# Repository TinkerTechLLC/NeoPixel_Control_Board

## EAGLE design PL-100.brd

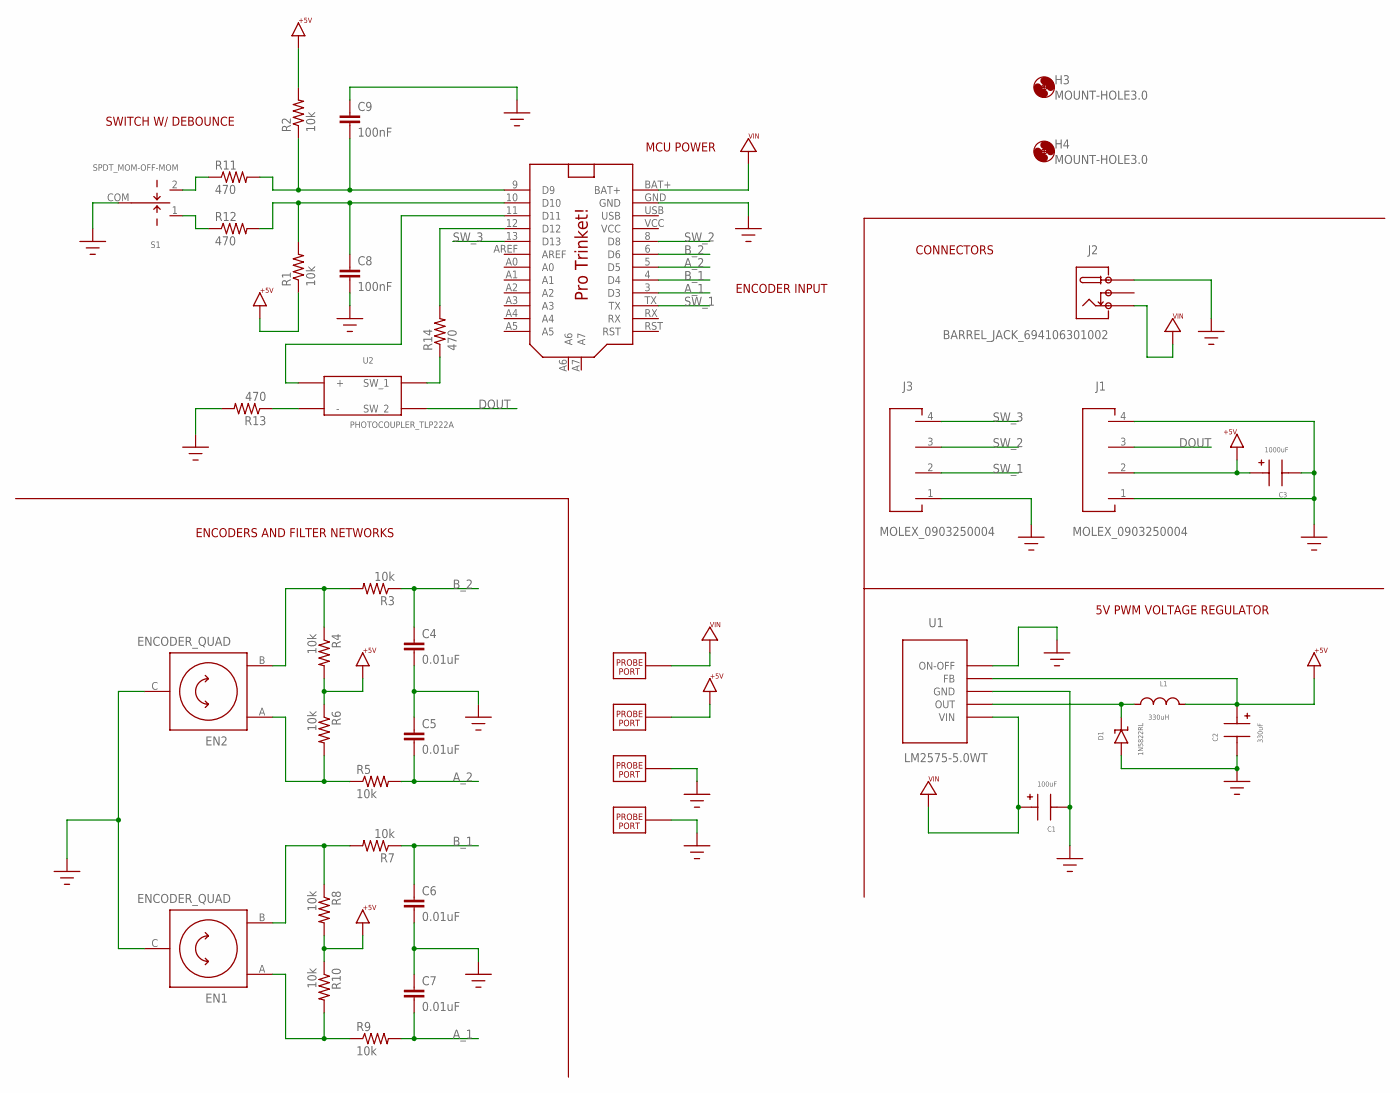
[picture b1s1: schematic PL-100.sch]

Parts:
+5V: PROBE_PORT
C1: 100uF; RADIAL_POL_6.3-DIA_2.5-SPACE
C2: 330uF; RADIAL_POL_8-DIA_3.5-SPACE
C3: 1000uF; RADIAL_POL_10-DIA_5-SPACE
C4, C5, C6, C7: 0.01uF; CAP-PTH-SMALLEZ
C8, C9: 100nF; CAP-PTH-SMALL
D1: 1N5822RL; DO-201AD_AXIAL
EN1, EN2: ENCODER_QUAD; PEC11R-4015F-N0024
GND1, GND2: PROBE_PORT
H3, H4: MOUNT-HOLE3.0; 3,0
J1, J3: MOLEX_0903250004; 0903250004
J2: BARREL_JACK_694106301002
L1: 330uH; INDUCT_AXIAL_28-SPACING
R1, R2, R3, R4, R5, R6, R7, R8, R9, R10: 10k; AXIAL-0.4
R11, R12, R13, R14: 470; AXIAL-0.4
S1: SPDT_MOM-OFF-MOM; 100SP4T6B11M2QEH
U1: LM2575-5.0WT; TO-220-5
U2: PHOTOCOUPLER_TLP222A; DIP-4
U$2: PRO_TRINKET; PROTRINKET
VIN: PROBE_PORT

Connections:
3: J2.3
+5V: +5V.P$1, C2.+, C3.+, J1.2, L1.2, R1.P$1 (1), R2.P$2 (2), R4.P$2 (2), R6.P$1 (1), R8.P$2 (2), R10.P$1 (1), U1.4 (FB)
A_1: C7.2, R9.P$2 (2), U$2.3 (D3)
A_2: C5.2, R5.P$2 (2), U$2.5 (D5)
B_1: C6.1, R7.P$1 (1), U$2.4 (D4)
B_2: C4.1, R3.P$1 (1), U$2.6 (D6)
DOUT: J1.3, U2.4 (SW_2)
GND: C1.-, C2.-, C3.-, C4.2, C5.1, C6.2, C7.1, C8.2, C9.1, D1.+, EN1.C (2), EN2.C (2), GND1.P$1, GND2.P$1, J1.1, J1.4, J2.1, J3.1, R13.P$2 (2), S1.COM, U1.3 (GND), U1.5 (ON-OFF), U$2.GND
unnamed: D1.-, L1.1, U1.2 (OUT)
unnamed: C9.2, R2.P$1 (1), R11.P$2 (2), U$2.9 (D9)
unnamed: C8.1, R1.P$2 (2), R12.P$2 (2), U$2.10 (D10)
unnamed: EN2.B (3), R3.P$2 (2), R4.P$1 (1)
unnamed: EN2.A (1), R5.P$1 (1), R6.P$2 (2)
unnamed: EN1.B (3), R7.P$2 (2), R8.P$1 (1)
unnamed: EN1.A (1), R9.P$1 (1), R10.P$2 (2)
unnamed: R11.P$1 (1), S1.2 (MOM_2)
unnamed: R12.P$1 (1), S1.1 (MOM_1)
unnamed: R13.P$1 (1), U2.2 (-)
unnamed: R14.P$2 (2), U$2.12 (D12)
unnamed: R14.P$1 (1), U2.3 (SW_1)
unnamed: U2.1 (+), U$2.11 (D11)
SW_1: J3.2, U$2.TX
SW_2: J3.3, U$2.8 (D8)
SW_3: J3.4, U$2.13 (D13)
USB: U$2.USB
VCC: U$2.VCC
VIN: C1.+, J2.2, U1.1 (VIN), U$2.BAT+, VIN.P$1

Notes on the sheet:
5V PWM VOLTAGE REGULATOR
ENCODERS AND FILTER NETWORKS
CONNECTORS
SWITCH W/ DEBOUNCE
ENCODER INPUT
MCU POWER

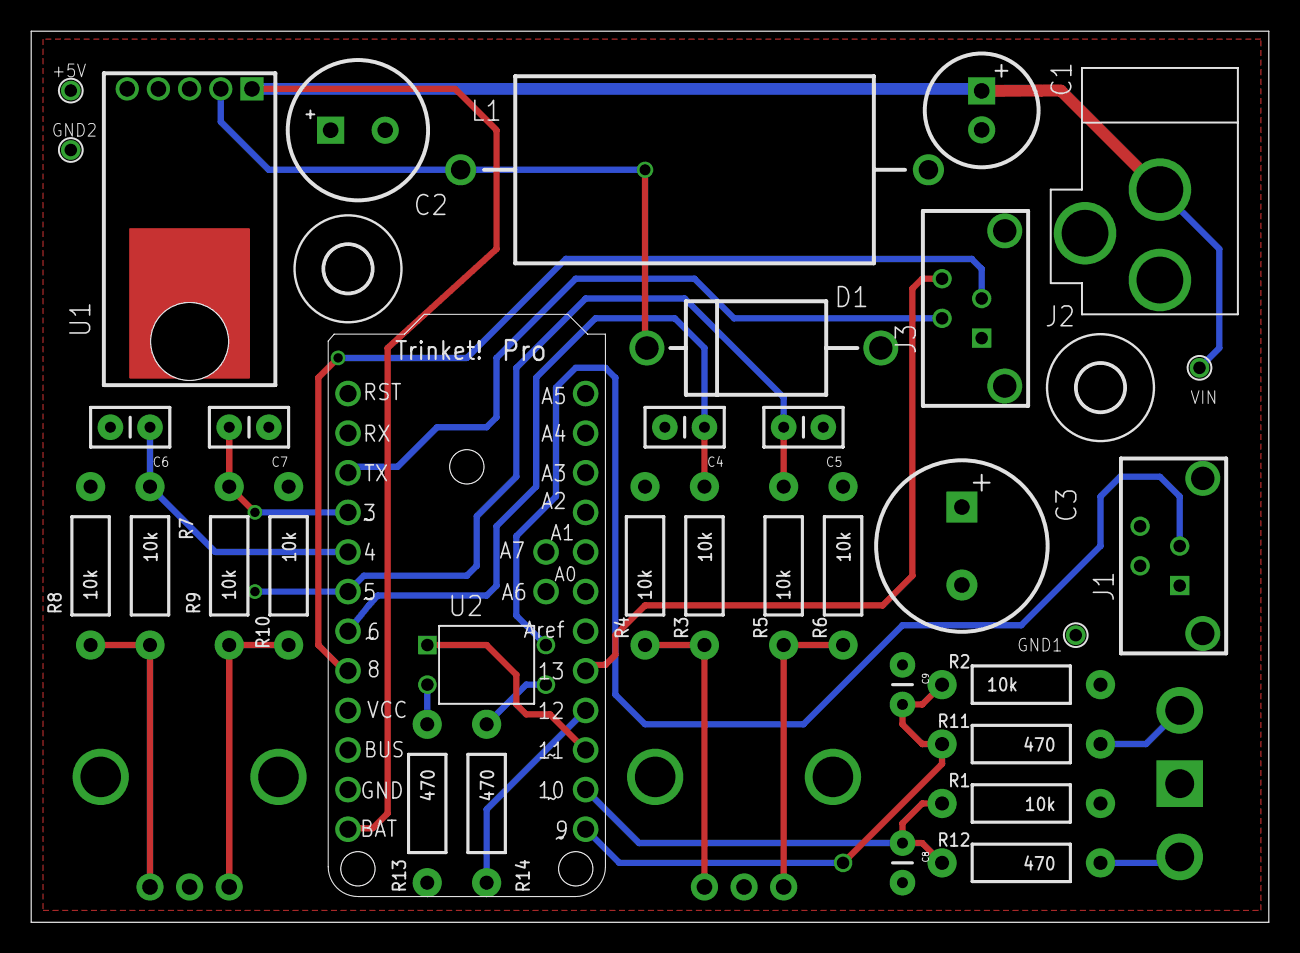
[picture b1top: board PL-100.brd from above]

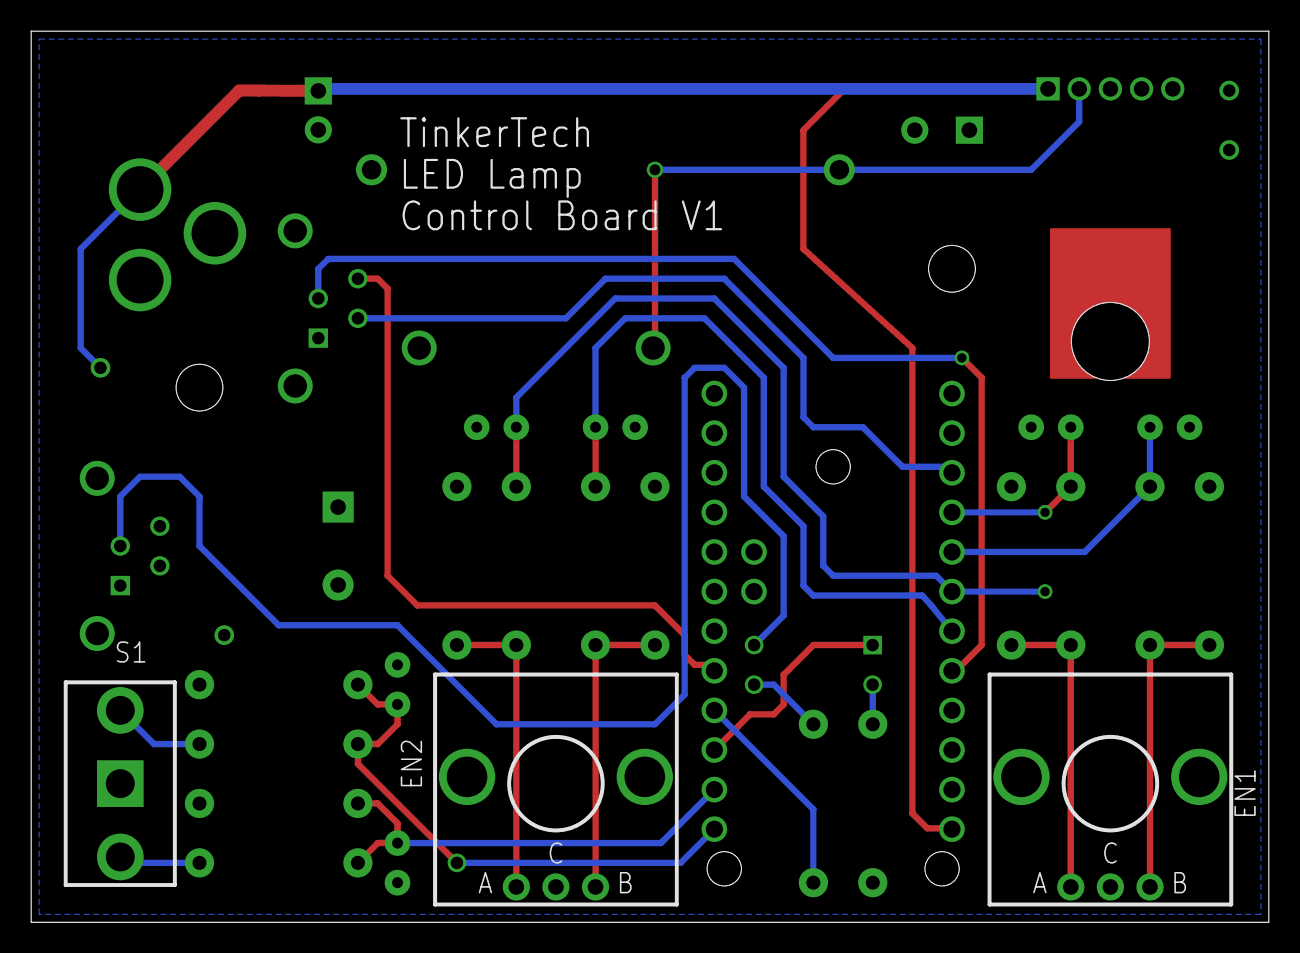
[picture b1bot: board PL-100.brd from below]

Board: 2 copper layers, 79.4 x 57.1 mm, 40 parts (3 on the bottom side), 24 nets.

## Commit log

2016-12-16 :space_invader: Added .gitattributes & .gitignore files

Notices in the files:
parts and their libraries:
SparkFun-Passives: Licensing: Creative Commons ShareAlike 4.0 International - https://creativecommons.org/licenses/by-sa/4.0
